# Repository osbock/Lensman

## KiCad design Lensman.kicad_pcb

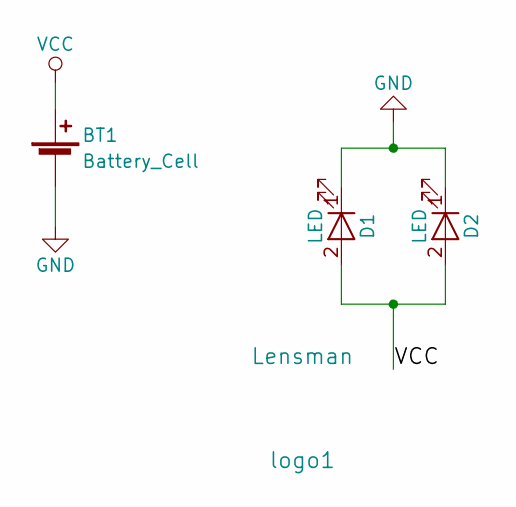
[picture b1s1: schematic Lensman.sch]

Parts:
BT1: Battery_Cell; BK-913
D1, D2: LED; LED_D5.0mm
logo1: Lensman; LOGO

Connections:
GND: BT1.2 (-), D1.1 (K), D2.1 (K)
VCC: BT1.1 (+), D1.2 (A), D2.2 (A)

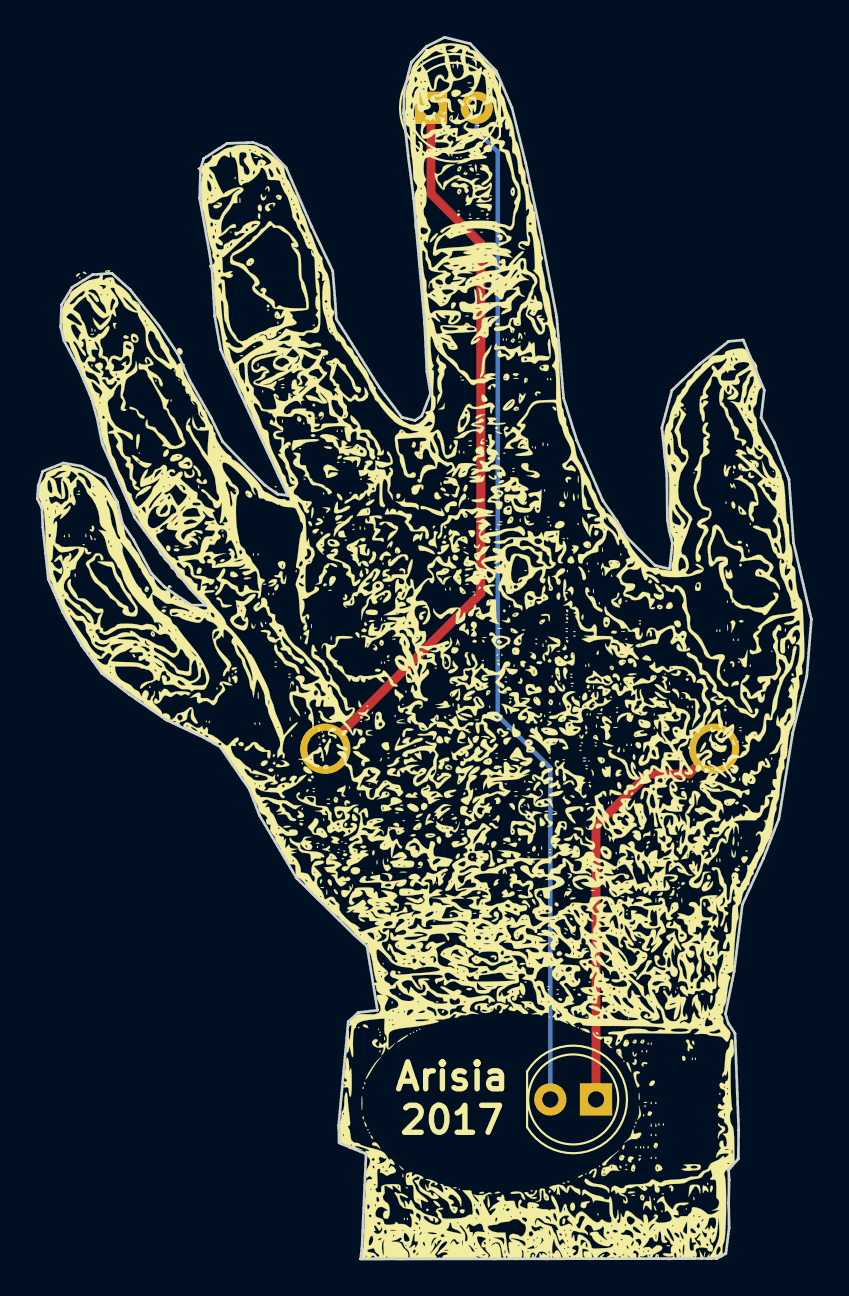
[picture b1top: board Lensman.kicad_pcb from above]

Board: 2 copper layers, 43.0 x 67.9 mm, 4 parts (1 on the bottom side), 2 nets.
